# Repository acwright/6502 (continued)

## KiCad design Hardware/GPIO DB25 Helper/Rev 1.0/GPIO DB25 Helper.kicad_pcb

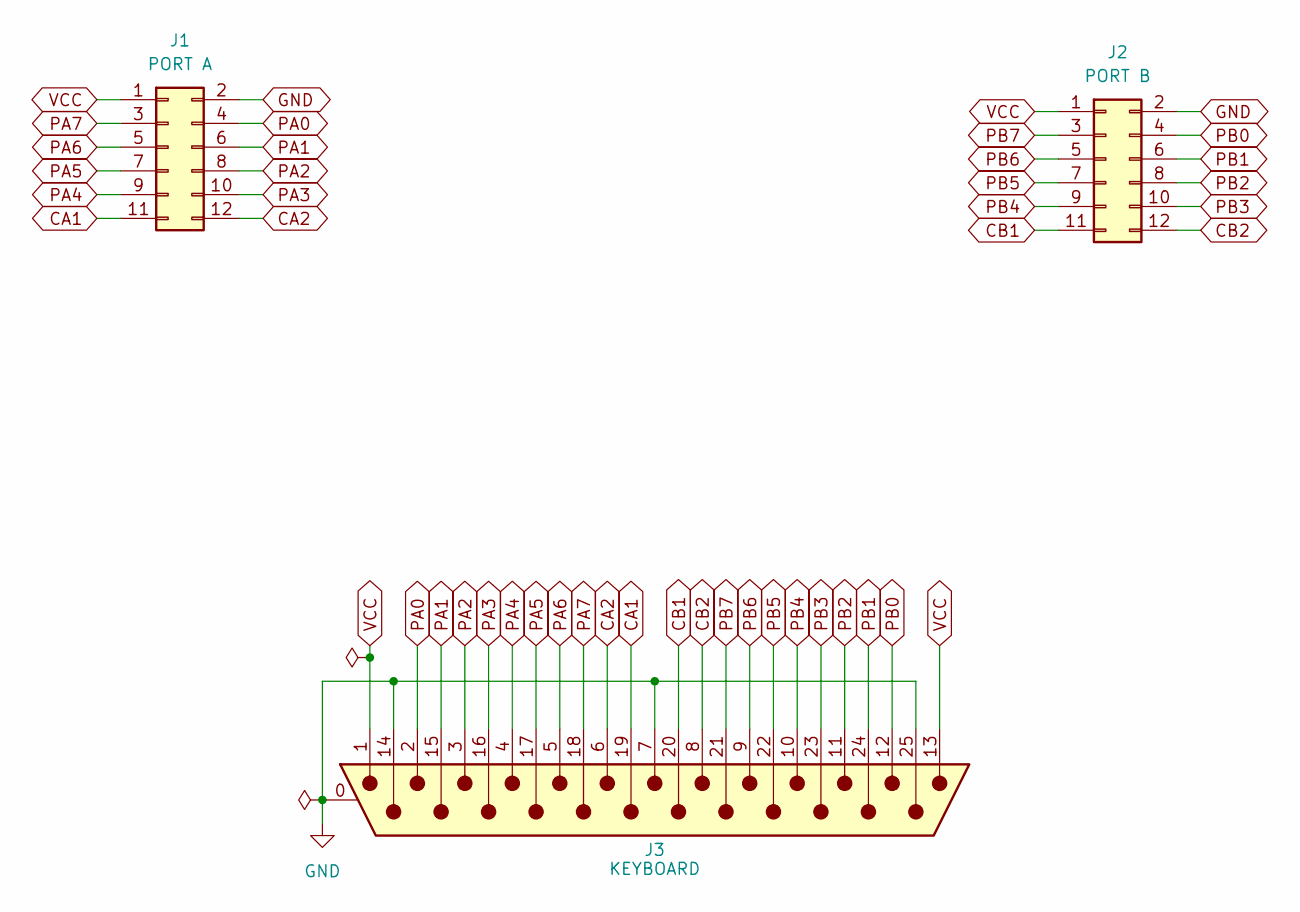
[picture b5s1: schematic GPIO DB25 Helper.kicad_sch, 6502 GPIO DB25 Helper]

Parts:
J1: PORT A; 6502 GPIO Connector
J2: PORT B; 6502 GPIO Connector
J3: KEYBOARD; DSUB-25_Pins_Horizontal_P2.77x2.84mm_EdgePinOffset7.70mm_Ho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; MPN D25P33E4GX00LF; Digikey 609-1505-ND

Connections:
CA1: J1.11, J3.19
CA2: J1.12, J3.6
CB1: J2.11, J3.20
CB2: J2.12, J3.8
GND: J1.2, J2.2, J3.0 (PAD), J3.7, J3.14, J3.25
PA0: J1.4, J3.2
PA1: J1.6, J3.15
PA2: J1.8, J3.3
PA3: J1.10, J3.16
PA4: J1.9, J3.4
PA5: J1.7, J3.17
PA6: J1.5, J3.5
PA7: J1.3, J3.18
PB0: J2.4, J3.12
PB1: J2.6, J3.24
PB2: J2.8, J3.11
PB3: J2.10, J3.23
PB4: J2.9, J3.10
PB5: J2.7, J3.22
PB6: J2.5, J3.9
PB7: J2.3, J3.21
VCC: J1.1, J2.1, J3.1, J3.13

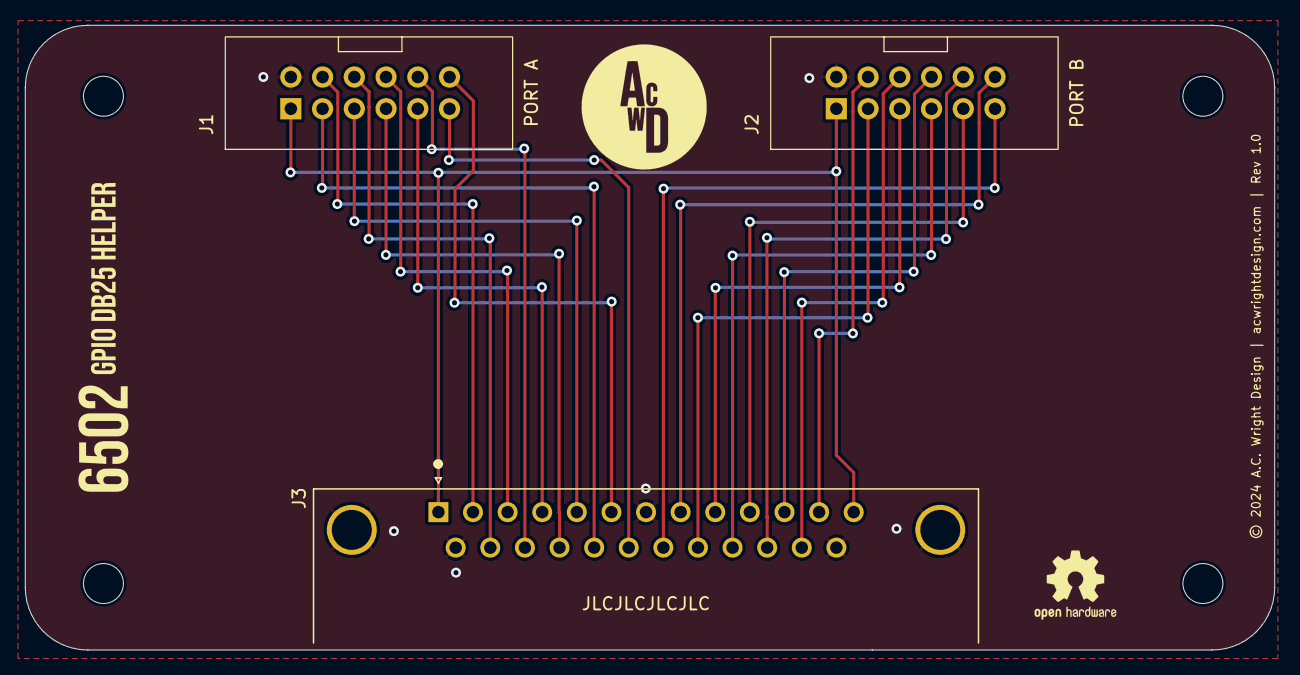
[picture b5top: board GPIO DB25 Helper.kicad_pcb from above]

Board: 2 copper layers, 100.0 x 50.0 mm, 7 parts (0 on the bottom side), 22 nets.

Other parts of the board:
H1, H2, H3, H4: MountingHole; MountingHole_3.2mm_M3

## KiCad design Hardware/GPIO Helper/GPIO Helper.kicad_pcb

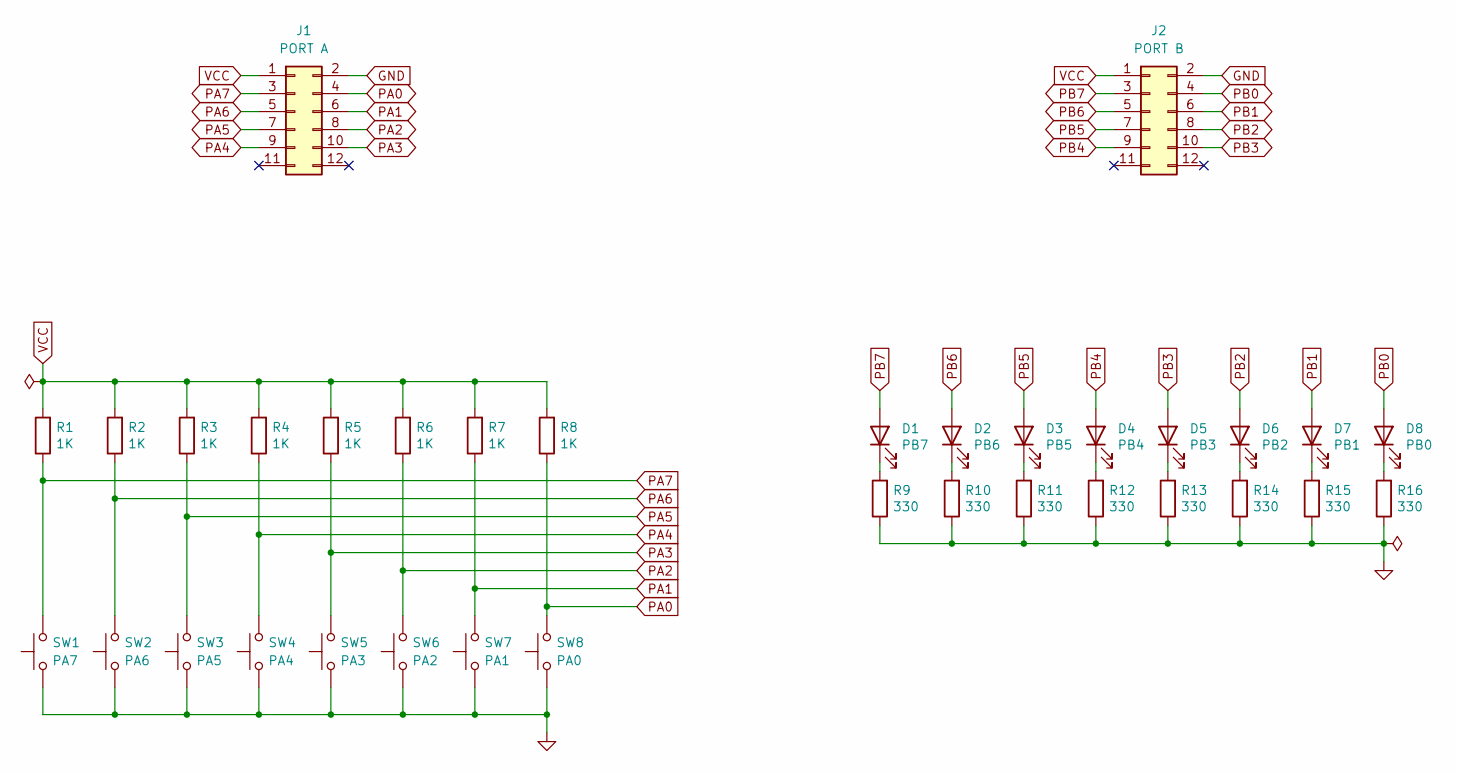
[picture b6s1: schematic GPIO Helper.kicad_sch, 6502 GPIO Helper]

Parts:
D1: PB7; LED_D3.0mm
D2: PB6; LED_D3.0mm
D3: PB5; LED_D3.0mm
D4: PB4; LED_D3.0mm
D5: PB3; LED_D3.0mm
D6: PB2; LED_D3.0mm
D7: PB1; LED_D3.0mm
D8: PB0; LED_D3.0mm
J1: PORT A; 6502 GPIO Connector
J2: PORT B; 6502 GPIO Connector
R1, R2, R3, R4, R5, R6, R7, R8: 1K; R_Axial_DIN0204_L3.6mm_D1.6mm_P5.08mm_Horizontal
R9, R10, R11, R12, R13, R14, R15, R16: 330; R_Axial_DIN0204_L3.6mm_D1.6mm_P5.08mm_Horizontal
SW1: PA7; SW_PUSH_6mm
SW2: PA6; SW_PUSH_6mm
SW3: PA5; SW_PUSH_6mm
SW4: PA4; SW_PUSH_6mm
SW5: PA3; SW_PUSH_6mm
SW6: PA2; SW_PUSH_6mm
SW7: PA1; SW_PUSH_6mm
SW8: PA0; SW_PUSH_6mm

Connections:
GND: J1.2, J2.2, R9.1, R10.1, R11.1, R12.1, R13.1, R14.1, R15.1, R16.1, SW1.1, SW2.1, SW3.1, SW4.1, SW5.1, SW6.1, SW7.1, SW8.1
unnamed: D1.1 (K), R9.2
unnamed: D2.1 (K), R10.2
unnamed: D3.1 (K), R11.2
unnamed: D4.1 (K), R12.2
unnamed: D5.1 (K), R13.2
unnamed: D6.1 (K), R14.2
unnamed: D7.1 (K), R15.2
unnamed: D8.1 (K), R16.2
PA0: J1.4, R8.1, SW8.2
PA1: J1.6, R7.1, SW7.2
PA2: J1.8, R6.1, SW6.2
PA3: J1.10, R5.1, SW5.2
PA4: J1.9, R4.1, SW4.2
PA5: J1.7, R3.1, SW3.2
PA6: J1.5, R2.1, SW2.2
PA7: J1.3, R1.1, SW1.2
PB0: D8.2 (A), J2.4
PB1: D7.2 (A), J2.6
PB2: D6.2 (A), J2.8
PB3: D5.2 (A), J2.10
PB4: D4.2 (A), J2.9
PB5: D3.2 (A), J2.7
PB6: D2.2 (A), J2.5
PB7: D1.2 (A), J2.3
VCC: J1.1, J2.1, R1.2, R2.2, R3.2, R4.2, R5.2, R6.2, R7.2, R8.2

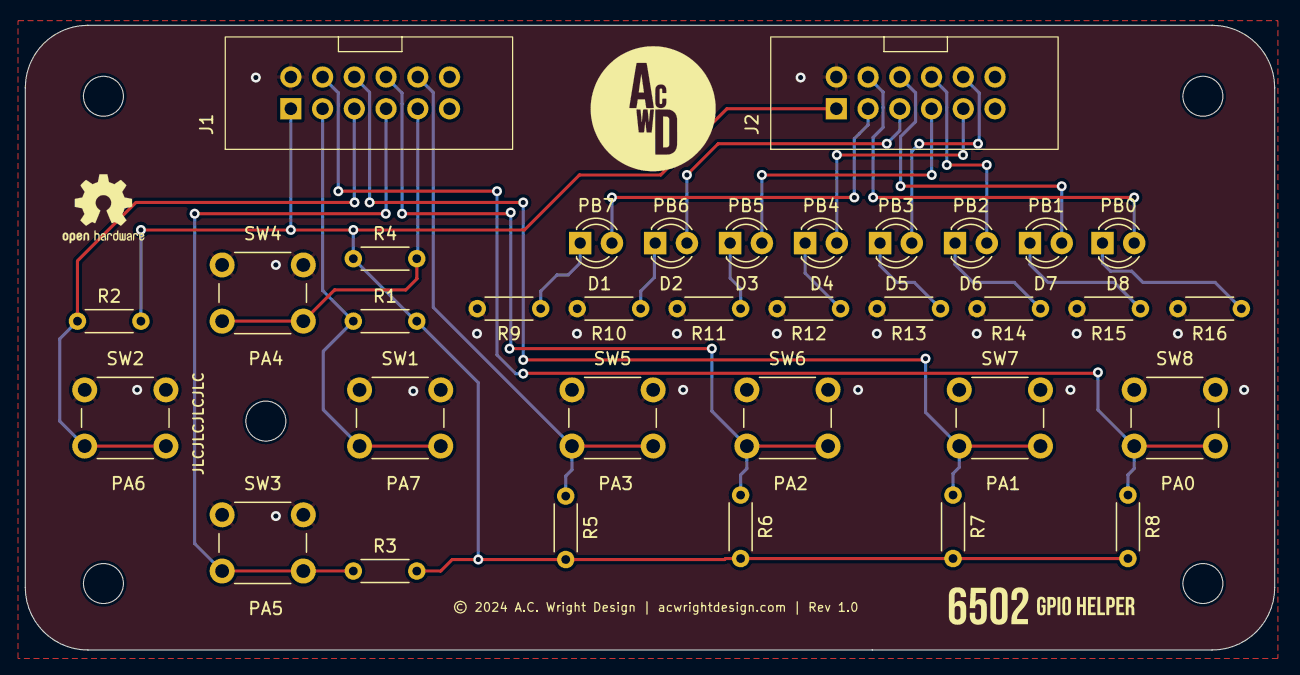
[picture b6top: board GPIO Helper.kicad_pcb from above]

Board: 2 copper layers, 100.0 x 50.0 mm, 34 parts (0 on the bottom side), 26 nets.
